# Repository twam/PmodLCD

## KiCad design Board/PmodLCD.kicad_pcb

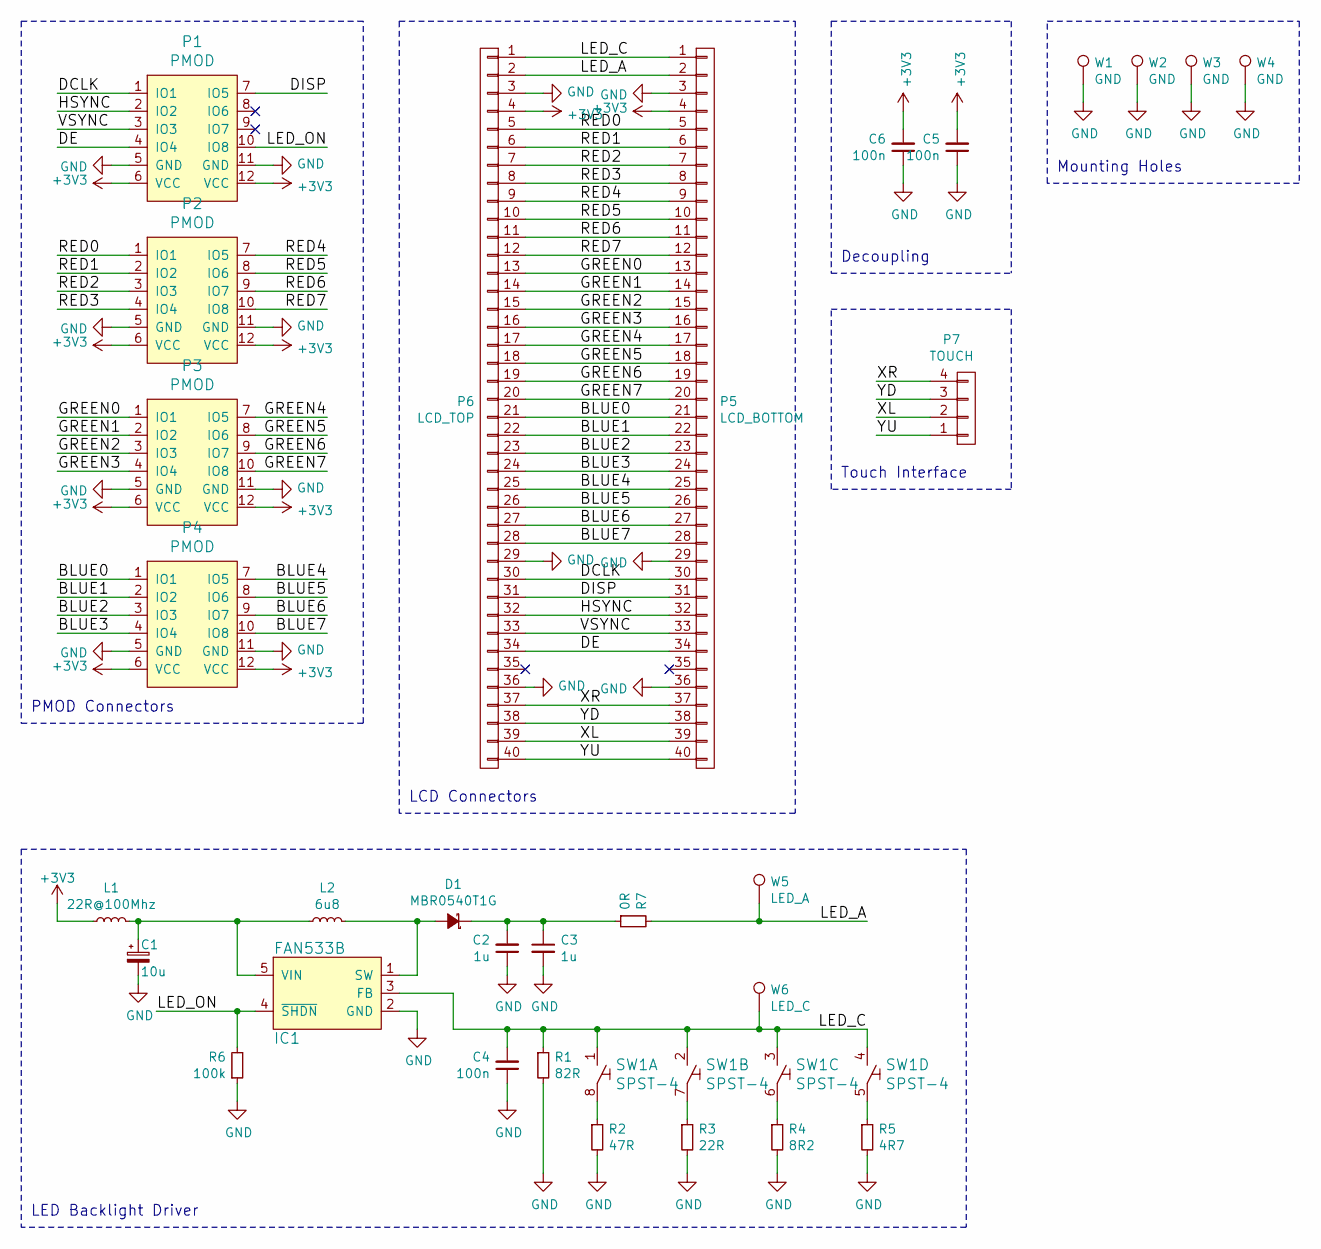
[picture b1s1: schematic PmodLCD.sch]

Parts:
C1: 10u; TantalC_SizeB_EIA-3528_Reflow
C2, C3: 1u; C_0603
C4, C5, C6: 100n; C_0603
D1: MBR0540T1G; SOD-123
IC1: FAN533B; SOT-23-5
L1: 22R@100Mhz; R_0603
L2: 6u8; IFSC-1111AB-01
P1, P2, P3, P4: PMOD; PMOD-DUAL-MALE
P5: LCD_BOTTOM; 4-1734592-0
P6: LCD_TOP; 4-1734839-0
P7: TOUCH; Pin_Header_Straight_1x04
R1: 82R; R_0603
R2: 47R; R_0603
R3: 22R; R_0603
R4: 8R2; R_0603
R5: 4R7; R_0603
R6: 100k; R_0603
R7: 0R; R_0603
SW1: SPST-4; ADF04S04
W1, W2, W3, W4: GND; MountingHole_3-2mm_M3_Pad
W5: LED_A; MountingHole_3-2mm_M3_Pad
W6: LED_C; MountingHole_3-2mm_M3_Pad

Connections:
+3V3: C5.2, C6.2, L1.1, P1.6 (VCC), P1.12 (VCC), P2.6 (VCC), P2.12 (VCC), P3.6 (VCC), P3.12 (VCC), P4.6 (VCC), P4.12 (VCC), P5.4, P6.4
/BLUE0: P4.1 (IO1), P5.21, P6.21
/BLUE1: P4.2 (IO2), P5.22, P6.22
/BLUE2: P4.3 (IO3), P5.23, P6.23
/BLUE3: P4.4 (IO4), P5.24, P6.24
/BLUE4: P4.7 (IO5), P5.25, P6.25
/BLUE5: P4.8 (IO6), P5.26, P6.26
/BLUE6: P4.9 (IO7), P5.27, P6.27
/BLUE7: P4.10 (IO8), P5.28, P6.28
/DCLK: P1.1 (IO1), P5.30, P6.30
/DE: P1.4 (IO4), P5.34, P6.34
/DISP: P1.7 (IO5), P5.31, P6.31
/GREEN0: P3.1 (IO1), P5.13, P6.13
/GREEN1: P3.2 (IO2), P5.14, P6.14
/GREEN2: P3.3 (IO3), P5.15, P6.15
/GREEN3: P3.4 (IO4), P5.16, P6.16
/GREEN4: P3.7 (IO5), P5.17, P6.17
/GREEN5: P3.8 (IO6), P5.18, P6.18
/GREEN6: P3.9 (IO7), P5.19, P6.19
/GREEN7: P3.10 (IO8), P5.20, P6.20
/HSYNC: P1.2 (IO2), P5.32, P6.32
/LED_A: P5.2, P6.2, R7.2, W5.1
/LED_C: C4.2, IC1.3 (FB), P5.1, P6.1, R1.1, SW1.1, SW1.2, SW1.3, SW1.4, W6.1
/LED_ON: IC1.4 (~SHDN), P1.10 (IO8), R6.2
/RED0: P2.1 (IO1), P5.5, P6.5
/RED1: P2.2 (IO2), P5.6, P6.6
/RED2: P2.3 (IO3), P5.7, P6.7
/RED3: P2.4 (IO4), P5.8, P6.8
/RED4: P2.7 (IO5), P5.9, P6.9
/RED5: P2.8 (IO6), P5.10, P6.10
/RED6: P2.9 (IO7), P5.11, P6.11
/RED7: P2.10 (IO8), P5.12, P6.12
/VSYNC: P1.3 (IO3), P5.33, P6.33
/XL: P5.39, P6.39, P7.2
/XR: P5.37, P6.37, P7.4
/YD: P5.38, P6.38, P7.3
/YU: P5.40, P6.40, P7.1
GND: C1.2, C2.1, C3.2, C4.1, C5.1, C6.1, IC1.2 (GND), P1.5 (GND), P1.11 (GND), P2.5 (GND), P2.11 (GND), P3.5 (GND), P3.11 (GND), P4.5 (GND), P4.11 (GND), P5.3, P5.29, P5.36, P6.3, P6.29, P6.36, R1.2, R2.2, R3.2, R4.2, R5.2, R6.1, W1.1, W2.1, W3.1, W4.1
unnamed: C1.1, IC1.5 (VIN), L1.2, L2.1
unnamed: C2.2, C3.1, D1.1 (K), R7.1
unnamed: D1.2 (A), IC1.1 (SW), L2.2
unnamed: R2.1, SW1.8
unnamed: R3.1, SW1.7
unnamed: R4.1, SW1.6
unnamed: R5.1, SW1.5

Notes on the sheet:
LED Backlight Driver
PMOD Connectors
LCD Connectors
Decoupling
Mounting Holes
Touch Interface

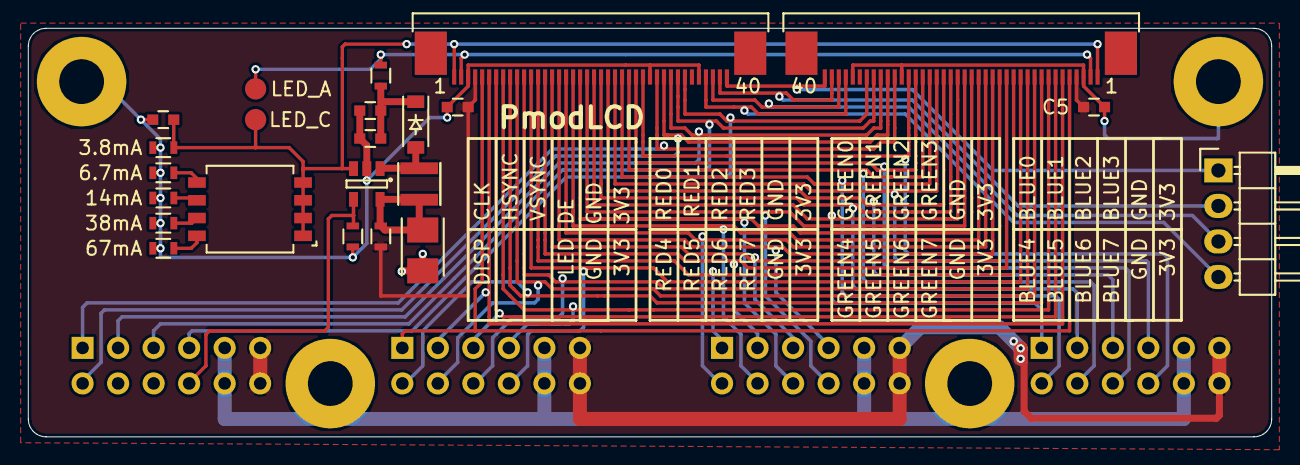
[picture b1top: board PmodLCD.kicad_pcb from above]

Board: 2 copper layers, 88.9 x 29.2 mm, 31 parts (0 on the bottom side), 45 nets.

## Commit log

2016-01-24 Changed Switch Footprint

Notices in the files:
Board/PmodLCD.kicad_pcb:
License: CC BY-SA 4.0
CC-BY-SA 4.0
